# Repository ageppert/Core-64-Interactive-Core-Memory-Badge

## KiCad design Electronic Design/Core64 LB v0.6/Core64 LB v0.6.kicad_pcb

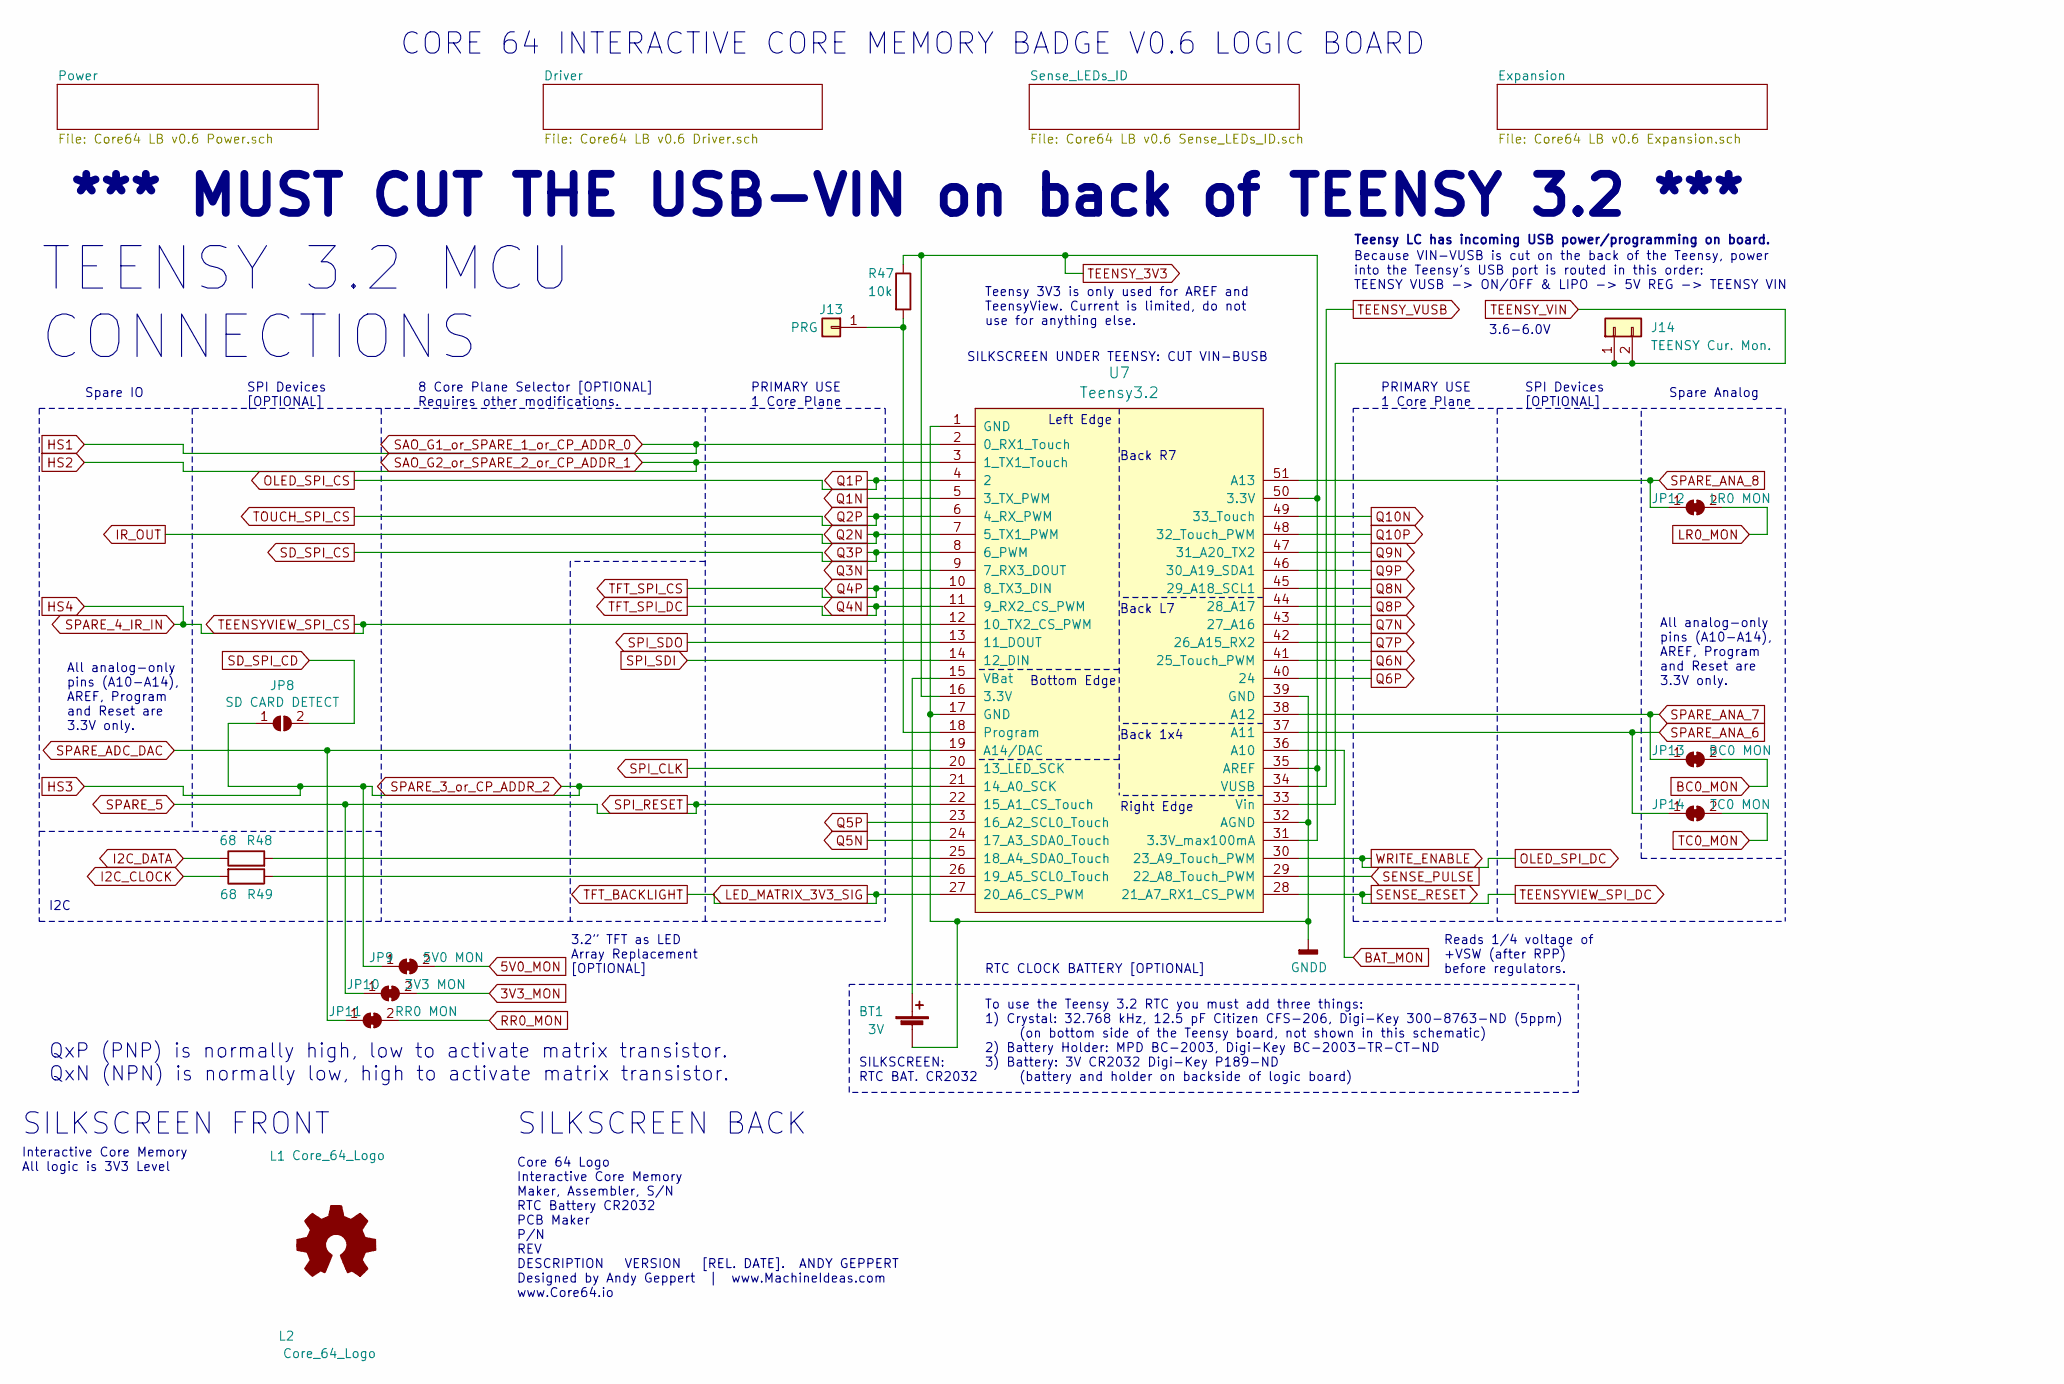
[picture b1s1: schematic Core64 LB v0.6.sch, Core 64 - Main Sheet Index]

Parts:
BT1: 3V; BatteryHolder_MPD_BC2003_1x2032; MPN MPD BC-2003
J13: PRG; PinSocket_1x01_P2.54mm_Vertical
J14: TEENSY Cur. Mon.; PinSocket_1x02_P2.54mm_Vertical
JP8: SD CARD DETECT; SolderJumper-2_P1.3mm_Open_RoundedPad1.0x1.5mm
JP9: 5V0 MON; SolderJumper-2_P1.3mm_Bridged_Pad1.0x1.5mm
JP10: 3V3 MON; SolderJumper-2_P1.3mm_Bridged_Pad1.0x1.5mm
JP11: RR0 MON; SolderJumper-2_P1.3mm_Bridged_Pad1.0x1.5mm
JP12: LR0 MON; SolderJumper-2_P1.3mm_Bridged_Pad1.0x1.5mm
JP13: BC0 MON; SolderJumper-2_P1.3mm_Bridged_Pad1.0x1.5mm
JP14: TC0 MON; SolderJumper-2_P1.3mm_Bridged_Pad1.0x1.5mm
L1: Core_64_Logo; Core64_Logo
L2: Core_64_Logo; Core64_Logo_9mm_tall
L4: Logo_Open_Hardware_Small; OSHW-Logo2_7.3x6mm_SilkScreen
R47: 10k; R_0805_2012Metric
R48, R49: 68; R_0805_2012Metric
U7: Teensy3.2; Teensy30_31_32_LC_SMD_SOCKETS

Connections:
3V3: JP10.2 (B); also elsewhere on the board
5V0: J14.1, J14.2, U7.33 (Vin); also elsewhere on the board
5V0_MON: JP9.2 (B); also elsewhere on the board
BAT_MON: U7.36 (A10); also elsewhere on the board
BC0_MON: JP13.2 (B); also elsewhere on the board
I2C_CLOCK: R49.2; also elsewhere on the board
I2C_DATA: R48.1; also elsewhere on the board
IR_OUT: U7.7 (5_TX1_PWM); also elsewhere on the board
LR0_MON: JP12.2 (B); also elsewhere on the board
unnamed: BT1.1 (+), U7.15 (VBat)
unnamed: J13.1, R47.2, U7.18 (Program)
unnamed: R48.2, U7.25 (18_A4_SDA0_Touch)
unnamed: R49.1, U7.26 (19_A5_SCL0_Touch)
OLED_SPI_CS: U7.4 (2); also elsewhere on the board
OLED_SPI_DC: U7.30 (23_A9_Touch_PWM); also elsewhere on the board
Q1N: U7.5 (3_TX_PWM); also elsewhere on the board
Q2P: U7.6 (4_RX_PWM); also elsewhere on the board
Q3N: U7.9 (7_RX3_DOUT); also elsewhere on the board
Q3P: U7.8 (6_PWM); also elsewhere on the board
Q4N: U7.11 (9_RX2_CS_PWM); also elsewhere on the board
Q4P: U7.10 (8_TX3_DIN); also elsewhere on the board
Q5N: U7.24 (17_A3_SDA0_Touch); also elsewhere on the board
Q5P: U7.23 (16_A2_SCL0_Touch); also elsewhere on the board
Q6N: U7.41 (25_Touch_PWM); also elsewhere on the board
Q6P: U7.40 (24); also elsewhere on the board
Q7N: U7.43 (27_A16); also elsewhere on the board
Q7P: U7.42 (26_A15_RX2); also elsewhere on the board
Q8N: U7.45 (29_A18_SCL1); also elsewhere on the board
Q8P: U7.44 (28_A17); also elsewhere on the board
Q9N: U7.47 (31_A20_TX2); also elsewhere on the board
Q9P: U7.46 (30_A19_SDA1); also elsewhere on the board
Q10N: U7.49 (33_Touch); also elsewhere on the board
Q10P: U7.48 (32_Touch_PWM); also elsewhere on the board
RR0_MON: JP11.2 (B); also elsewhere on the board
SD_SPI_CD: JP8.2 (B); also elsewhere on the board
SENSE_PULSE: U7.29 (22_A8_Touch_PWM); also elsewhere on the board
SENSE_RESET: U7.28 (21_A7_RX1_CS_PWM); also elsewhere on the board
SPARE_5: JP10.1 (A), U7.22 (15_A1_CS_Touch); also elsewhere on the board
SPARE_ADC_DAC: JP11.1 (A), U7.19 (A14/DAC); also elsewhere on the board
SPARE_ANA_6: JP14.1 (A), U7.37 (A11); also elsewhere on the board
SPARE_ANA_7: JP13.1 (A), U7.38 (A12); also elsewhere on the board
SPARE_ANA_8: JP12.1 (A), U7.51 (A13); also elsewhere on the board
SPI_CLK: U7.20 (13_LED_SCK); also elsewhere on the board
SPI_SDI: U7.14 (12_DIN); also elsewhere on the board
SPI_SDO: U7.13 (11_DOUT); also elsewhere on the board
TC0_MON: JP14.2 (B); also elsewhere on the board
TEENSY_3V3: R47.1, U7.16 (3.3V), U7.31 (3.3V_max100mA), U7.35 (AREF), U7.50 (3.3V); also elsewhere on the board
TEENSY_VUSB: U7.34 (VUSB); also elsewhere on the board

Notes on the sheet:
CORE 64 INTERACTIVE CORE MEMORY BADGE V0.6 LOGIC BOARD
Reads 1/4 voltage of +VSW (after RPP) before regulators.
Teensy LC has incoming USB power/programming on board.
TEENSY 3.2 MCU CONNECTIONS
*** MUST CUT THE USB-VIN on back of TEENSY 3.2 ***
Teensy 3V3 is only used for AREF and TeensyView. Current is limited, do not use for anything else.
PRIMARY USE 1 Core Plane
3.2” TFT as LED Array Replacement [OPTIONAL]
8 Core Plane Selector [OPTIONAL] Requires other modifications.
SILKSCREEN BACK
SILKSCREEN UNDER TEENSY: CUT VIN-BUSB
To use the Teensy 3.2 RTC you must add three things: 1) Crystal: 32.768 kHz, 12.5 pF Citizen CFS-206, Digi-Key 300-8763-ND (5ppm) (on bottom side of the Teensy board, not shown in this schematic) 2) Battery Holder: MPD BC-2003, Digi-Key BC-2003-TR-CT-ND 3) Battery: 3V CR2032 Digi-Key P189-ND (batte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
SILKSCREEN: RTC BAT. CR2032
SILKSCREEN FRONT
Core 64 Logo Interactive Core Memory Maker, Assembler, S/N RTC Battery CR2032 PCB Maker P/N REV DESCRIPTION VERSION [REL. DATE]. ANDY GEPPERT Designed by Andy Geppert | www.MachineIdeas.com www.Core64.io
Interactive Core Memory All logic is 3V3 Level
Spare Analog
Spare IO
SPI Devices [OPTIONAL]
RTC CLOCK BATTERY [OPTIONAL]
I2C
Because VIN-VUSB is cut on the back of the Teensy, power into the Teensy’s USB port is routed in this order: TEENSY VUSB -> ON/OFF & LIPO -> 5V REG -> TEENSY VIN
Left Edge
Bottom Edge
Right Edge
Back 1x4
Back L7
Back R7
QxP (PNP) is normally high, low to activate matrix transistor. QxN (NPN) is normally low, high to activate matrix transistor.
3.6-6.0V
All analog-only pins (A10-A14), AREF, Program and Reset are 3.3V only.

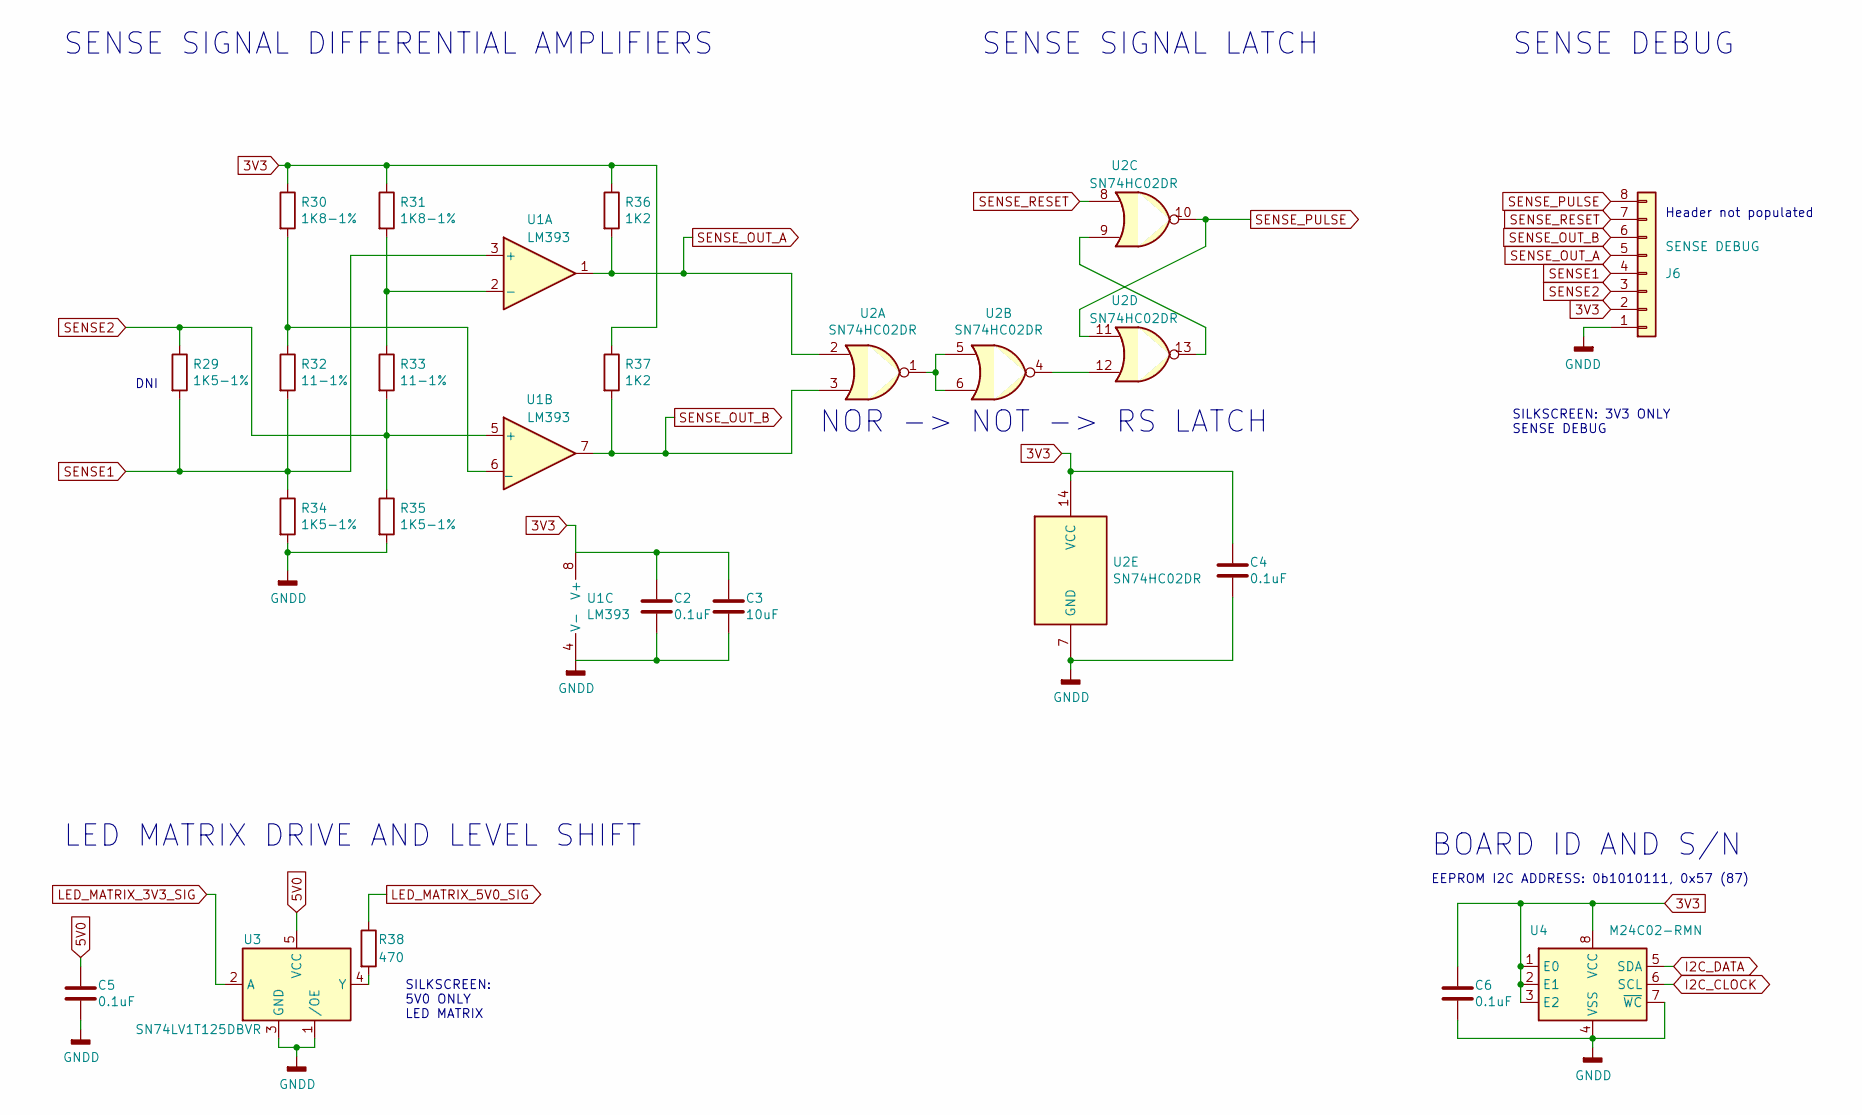
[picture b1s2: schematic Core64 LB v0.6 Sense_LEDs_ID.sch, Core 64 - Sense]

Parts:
C2, C4, C5, C6: 0.1uF; C_0805_2012Metric
C3: 10uF; C_0805_2012Metric
J6: SENSE DEBUG; PinSocket_1x08_P2.54mm_Vertical
R29, R34, R35: 1K5-1%; R_0805_2012Metric
R30, R31: 1K8-1%; R_0805_2012Metric
R32, R33: 11-1%; R_0805_2012Metric
R36, R37: 1K2; R_0805_2012Metric
R38: 470; R_0805_2012Metric
U1, U3: LM393; SOIC-8_W3.9mm; MPN LM393DT
U2: SN74HC02DR; SOIC-14_3.9x8.7mm_P1.27mm; MPN SN74HC02DR
U4: M24C02-RMN; SOIC-8_3.9x4.9mm_P1.27mm; MPN M24C02-WMN6TP

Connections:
3V3: C2.1, C3.1, C4.1, C6.1, J6.2, R30.1, R31.1, R36.1, R37.1, U1.8 (V+), U2.14 (VCC), U4.1 (E0), U4.2 (E1), U4.3 (E2), U4.8 (VCC); also elsewhere on the board
5V0: C5.1, U3.5 (VCC); also elsewhere on the board
I2C_CLOCK: U4.6 (SCL); also elsewhere on the board
I2C_DATA: U4.5 (SDA); also elsewhere on the board
LED_MATRIX_5V0_SIG: R38.1; also elsewhere on the board
unnamed: R30.2, R32.1, U1.6 (_)
unnamed: R38.2, U3.4 (Y)
unnamed: U2.1, U2.5, U2.6
unnamed: U2.4, U2.12
unnamed: U2.9, U2.13
SENSE2: J6.3, R29.1, R33.2, R35.1, U1.5 (+); also elsewhere on the board
SENSE_OUT_B: J6.6, R37.2, U1.7, U2.3
SENSE_PULSE: J6.8, U2.10, U2.11; also elsewhere on the board
SENSE_RESET: J6.7, U2.8; also elsewhere on the board

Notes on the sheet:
SENSE SIGNAL DIFFERENTIAL AMPLIFIERS
DNI
SENSE SIGNAL LATCH
SENSE DEBUG
SILKSCREEN: 3V3 ONLY SENSE DEBUG
NOR -> NOT -> RS LATCH
LED MATRIX DRIVE AND LEVEL SHIFT
SILKSCREEN: 5V0 ONLY LED MATRIX
BOARD ID AND S/N
EEPROM I2C ADDRESS: 0b1010111, 0x57 (87)
Header not populated

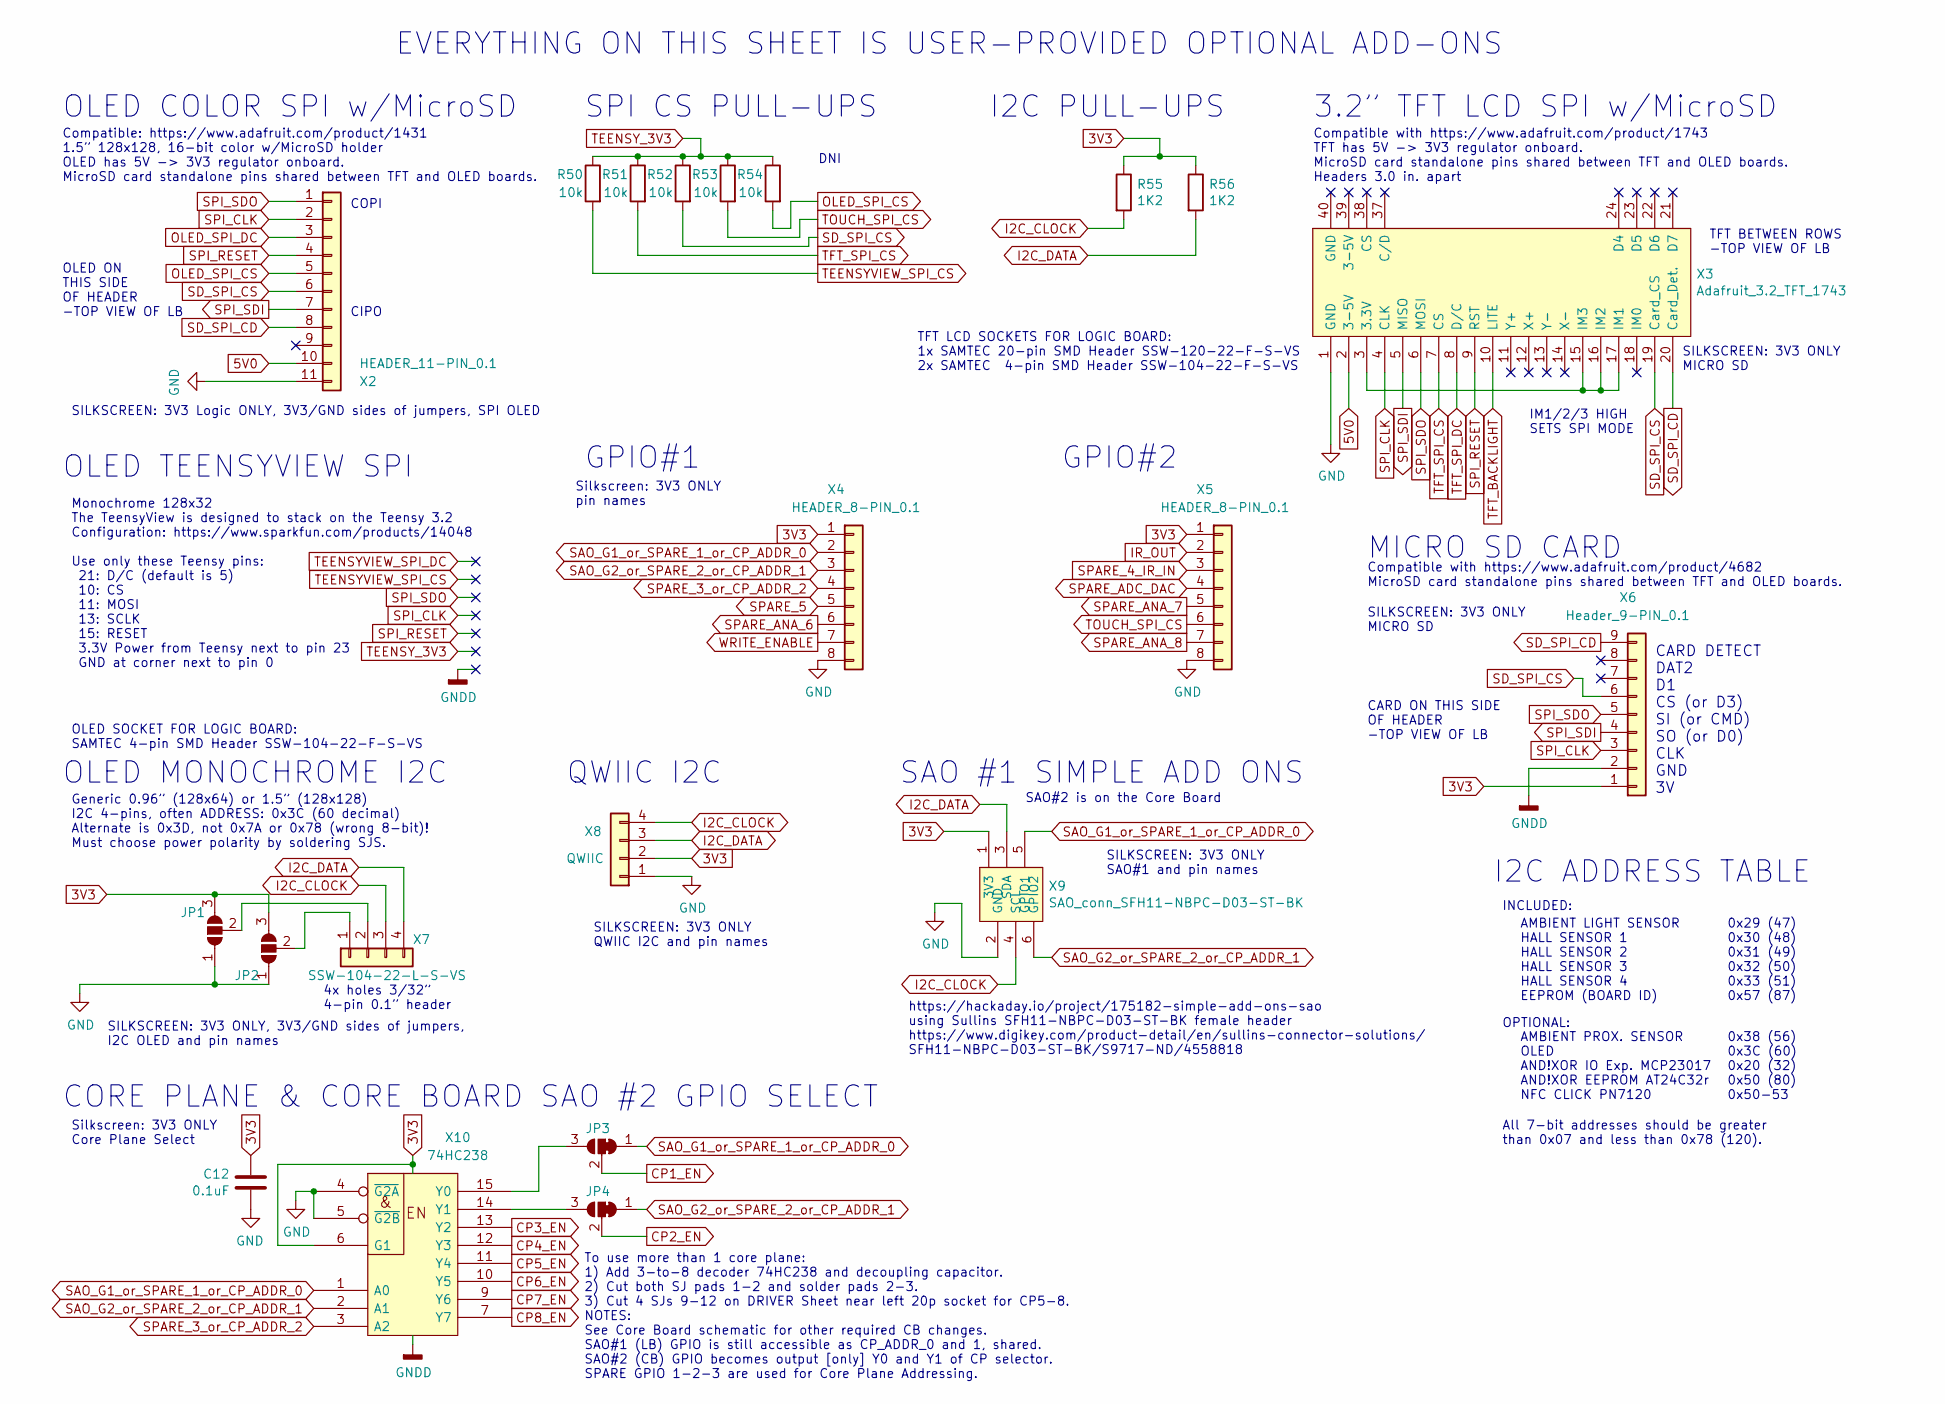
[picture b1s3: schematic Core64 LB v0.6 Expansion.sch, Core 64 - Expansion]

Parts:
C12: 0.1uF; C_0805_2012Metric
JP1, JP2: SolderJumper_3_Open; SolderJumper-3_P1.3mm_Open_Pad1.0x1.5mm_NumberLabels
JP3, JP4: SolderJumper_3_Open; SolderJumper-3_P1.3mm_Bridged12_RoundedPad1.0x1.5mm_NumberL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
R50, R51, R52, R53, R54: 10k; R_0805_2012Metric
R55, R56: 1K2; R_0805_2012Metric
X2: HEADER_11-PIN_0.1; PinSocket_1x11_P2.54mm_Vertical
X3: Adafruit_3.2_TFT_1743; Adafruit_3.2_TFT_Dual_PinHeader_1x20_P2.54mm_Vertical_SMD_P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; Manufacturer_Part_Number MIKROE-971; Mouser Part Number 932-MIKROE-971
X4, X5: HEADER_8-PIN_0.1; PinSocket_1x08_P2.54mm_Vertical
X6: Header_9-PIN_0.1; PinSocket_1x09_P2.54mm_Vertical
X7: SSW-104-22-L-S-VS; PinSocket_1x04_P2.54mm_Vertical_SMD_and_TH_Pin1Left
X8: QWIIC; JST_SH_SM04B-SRSS-TB_1x04-1MP_P1.00mm_Horizontal; MPN SM04B-SRSS-TB(LF)(SN)
X9: SAO_conn_SFH11-NBPC-D03-ST-BK; Badgelife-SAOv169-BADGE-2x3; MPN SFH11-NBPC-D03-ST-BK
X10: 74HC238; TSSOP-16-W4.40mm

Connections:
3V3: C12.1, JP1.3 (B), JP2.3 (B), R55.1, R56.1, X4.1, X5.1, X6.1, X8.2, X9.1 (3V3), X10.6 (G1), X10.16 (VCC); also elsewhere on the board
5V0: X2.10, X3.2 (3-5V); also elsewhere on the board
I2C_CLOCK: R55.2, X7.3, X8.4, X9.4 (SCL); also elsewhere on the board
I2C_DATA: R56.2, X7.4, X8.3, X9.3 (SDA); also elsewhere on the board
IR_OUT: X5.2; also elsewhere on the board
unnamed: X3.3 (3.3V), X3.15 (IM3), X3.16 (IM2), X3.17 (IM1)
unnamed: JP4.3 (B), X10.14 (Y1)
unnamed: JP3.3 (B), X10.15 (Y0)
OLED_SPI_CS: R54.2, X2.5; also elsewhere on the board
OLED_SPI_DC: X2.3, X4.7; also elsewhere on the board
Q2P: R53.2, X5.6; also elsewhere on the board
Q3P: R52.2, X2.6, X3.19 (Card_CS), X6.6; also elsewhere on the board
Q4N: X3.8 (D/C); also elsewhere on the board
Q4P: R51.2, X3.7 (CS); also elsewhere on the board
SD_SPI_CD: X2.8, X3.20 (Card_Det.), X6.9; also elsewhere on the board
SPARE_5: X2.4, X3.9 (RST), X4.5; also elsewhere on the board
SPARE_ADC_DAC: X5.4; also elsewhere on the board
SPARE_ANA_6: X4.6; also elsewhere on the board
SPARE_ANA_7: X5.5; also elsewhere on the board
SPARE_ANA_8: X5.7; also elsewhere on the board
SPI_CLK: X2.2, X3.4 (CLK), X6.3; also elsewhere on the board
SPI_SDI: X2.7, X3.5 (MISO), X6.4; also elsewhere on the board
SPI_SDO: X2.1, X3.6 (MOSI), X6.5; also elsewhere on the board
TEENSY_3V3: R50.1, R51.1, R52.1, R53.1, R54.1; also elsewhere on the board

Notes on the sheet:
CORE PLANE & CORE BOARD SAO #2 GPIO SELECT
SAO #1 SIMPLE ADD ONS
OLED MONOCHROME I2C
Generic 0.96” (128x64) or 1.5” (128x128) I2C 4-pins, often ADDRESS: 0x3C (60 decimal) Alternate is 0x3D, not 0x7A or 0x78 (wrong 8-bit)! Must choose power polarity by soldering SJS.
https://hackaday.io/project/175182-simple-add-ons-sao using Sullins SFH11-NBPC-D03-ST-BK female header https://www.digikey.com/product-detail/en/sullins-connector-solutions/ SFH11-NBPC-D03-ST-BK/S9717-ND/4558818
QWIIC I2C
MICRO SD CARD
Compatible with https://www.adafruit.com/product/4682 MicroSD card standalone pins shared between TFT and OLED boards.
SILKSCREEN: 3V3 ONLY, 3V3/GND sides of jumpers, I2C OLED and pin names
SILKSCREEN: 3V3 ONLY SAO#1 and pin names
Silkscreen: 3V3 ONLY pin names
OLED COLOR SPI w/MicroSD
3.2” TFT LCD SPI w/MicroSD
GPIO#1
EVERYTHING ON THIS SHEET IS USER-PROVIDED OPTIONAL ADD-ONS
To use more than 1 core plane: 1) Add 3-to-8 decoder 74HC238 and decoupling capacitor. 2) Cut both SJ pads 1-2 and solder pads 2-3. 3) Cut 4 SJs 9-12 on DRIVER Sheet near left 20p socket for CP5-8. NOTES: See Core Board schematic for other required CB changes. SAO#1 (LB) GPIO is still accessible as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
Silkscreen: 3V3 ONLY Core Plane Select
4x holes 3/32” 4-pin 0.1” header
SILKSCREEN: 3V3 ONLY QWIIC I2C and pin names
SILKSCREEN: 3V3 Logic ONLY, 3V3/GND sides of jumpers, SPI OLED
SILKSCREEN: 3V3 ONLY MICRO SD
SAO#2 is on the Core Board
CARD ON THIS SIDE OF HEADER -TOP VIEW OF LB
GPIO#2
Compatible with https://www.adafruit.com/product/1743 TFT has 5V -> 3V3 regulator onboard. MicroSD card standalone pins shared between TFT and OLED boards. Headers 3.0 in. apart
All 7-bit addresses should be greater than 0x07 and less than 0x78 (120).
AMBIENT LIGHT SENSOR HALL SENSOR 1 HALL SENSOR 2 HALL SENSOR 3 HALL SENSOR 4 EEPROM (BOARD ID)
0x29 (47) 0x30 (48) 0x31 (49) 0x32 (50) 0x33 (51) 0x57 (87)
INCLUDED:
OPTIONAL:
AMBIENT PROX. SENSOR OLED AND!XOR IO Exp. MCP23017 AND!XOR EEPROM AT24C32r NFC CLICK PN7120
0x38 (56) 0x3C (60) 0x20 (32) 0x50 (80) 0x50-53
I2C ADDRESS TABLE
OLED TEENSYVIEW SPI
Monochrome 128x32 The TeensyView is designed to stack on the Teensy 3.2 Configuration: https://www.sparkfun.com/products/14048 Use only these Teensy pins: 21: D/C (default is 5) 10: CS 11: MOSI 13: SCLK 15: RESET 3.3V Power from Teensy next to pin 23 GND at corner next to pin 0
Compatible: https://www.adafruit.com/product/1431 1.5” 128x128, 16-bit color w/MicroSD holder OLED has 5V -> 3V3 regulator onboard. MicroSD card standalone pins shared between TFT and OLED boards.
OLED ON THIS SIDE OF HEADER -TOP VIEW OF LB
I2C PULL-UPS
SPI CS PULL-UPS
DNI

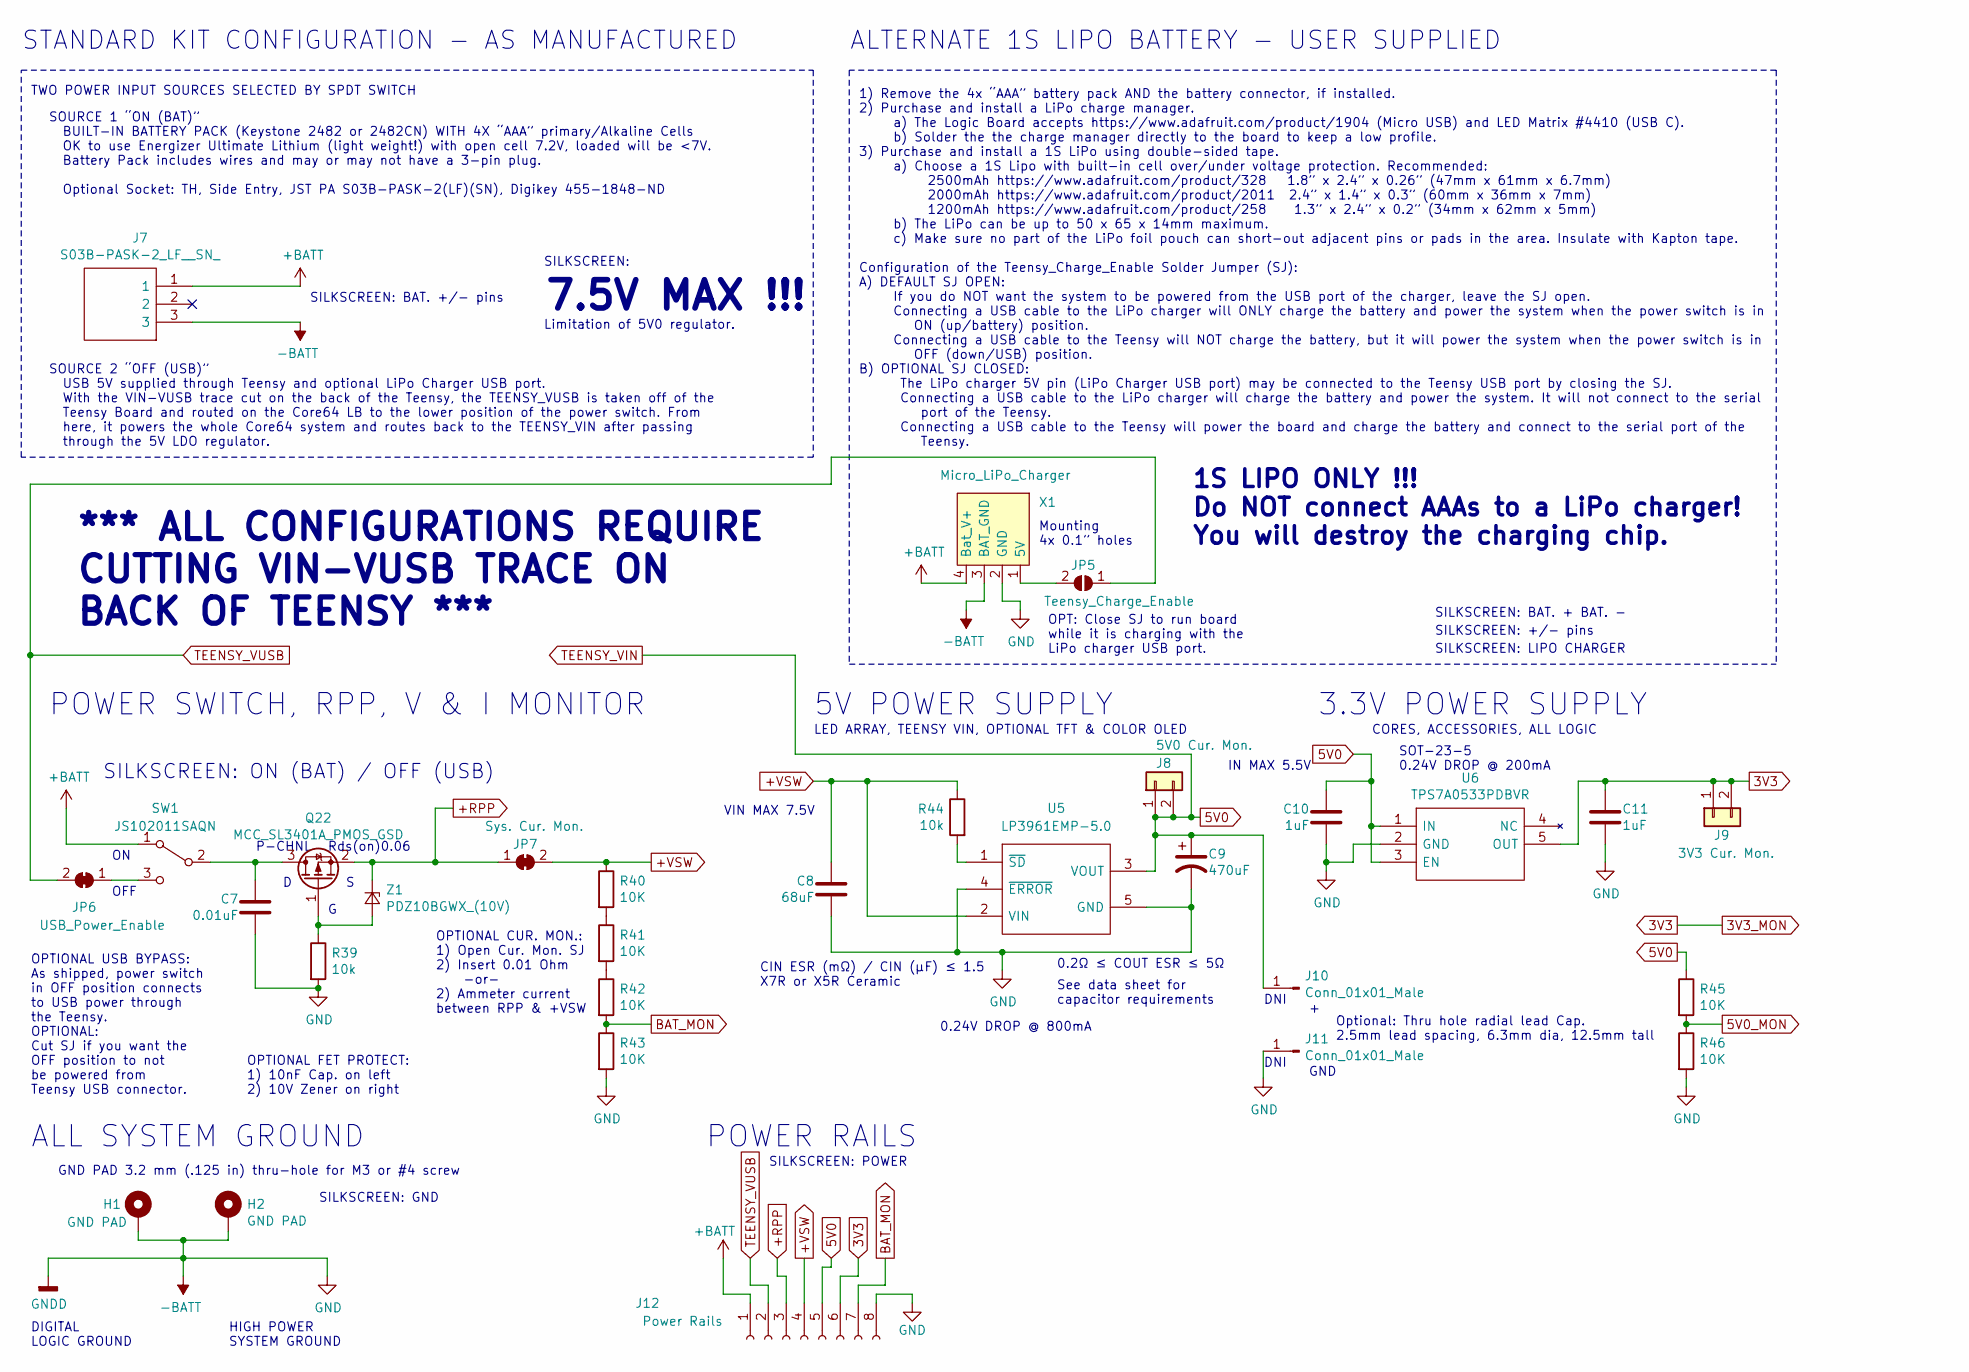
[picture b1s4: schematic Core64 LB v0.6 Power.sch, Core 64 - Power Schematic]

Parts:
C7: 0.01uF; C_0805_2012Metric
C8: 68uF; C_1206_3216Metric; MPN C3216X5R1A686M160AC
C9: 470uF; CP_Elec_6.3x7.7; MPN(Secondary) 6.3SEV330M6.3X8; Digikey 565-EMHL100ARA471MHA0GCT-ND
C10, C11: 1uF; C_0805_2012Metric
H1, H2: GND PAD; MountingHole_3.2mm_M3_Pad_Via
J7: S03B-PASK-2_LF__SN_; S03BPASK2LFSN_.075in_holes; Manufacturer_Part_Number S03B-PASK-2(LF)(SN)
J8: 5V0 Cur. Mon.; PinSocket_1x02_P2.54mm_Vertical
J9: 3V3 Cur. Mon.; PinSocket_1x02_P2.54mm_Vertical; MPN SN74HC02DR
J10, J11: Conn_01x01_Male; PinHeader_1x01_P2.54mm_Vertical_No_Registration
J12: Power Rails; PinSocket_1x08_P2.54mm_Vertical
JP5: Teensy_Charge_Enable; SolderJumper-2_P1.3mm_Open_RoundedPad1.0x1.5mm
JP6: USB_Power_Enable; SolderJumper-2_P1.3mm_Bridged_RoundedPad1.0x1.5mm
JP7: Sys. Cur. Mon.; SolderJumper-2_P1.3mm_Bridged_Pad1.0x1.5mm
Q22: MCC_SL3401A_PMOS_GSD; SOT-23-3; MPN SL3401A-TP
R39, R44: 10k; R_0805_2012Metric
R40, R41, R42, R43, R45, R46: 10K; R_0805_2012Metric
SW1: JS102011SAQN; SW_SPDT_CK-JS102011SAQN_Core64_Recessed; MPN JS102011SAQN
U5: LP3961EMP-5.0; SOT150P696X180-5N; Manufacturer_Part_Number LP3961EMP-5.0; Mouser Part Number 926-LP3961EMP-50
U6: TPS7A0533PDBVR; SOT95P280X145-5N; Manufacturer_Part_Number TPS7A0533PDBVR; Mouser Part Number 595-TPS7A0533PDBVR
X1: Micro_LiPo_Charger; Micro_LiPo_Charger_CornerSMD
Z1: PDZ10BGWX_(10V); SOD-123

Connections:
3V3: C11.1, J9.1, J9.2, J12.6, U6.5 (OUT); also elsewhere on the board
5V0: C9.1, C10.1, J8.1, J8.2, J10.1, J12.5, R45.1, U5.3 (VOUT), U6.1 (IN), U6.3 (EN); also elsewhere on the board
5V0_MON: R45.2, R46.1; also elsewhere on the board
+BATT: J7.1, J12.1, SW1.1 (A), X1.4 (Bat_V+); also elsewhere on the board
+RPP: J12.3, JP7.1 (A), Q22.2 (S), Z1.1 (K)
+VSW: C8.1, J12.4, JP7.2 (B), R40.1, R44.1, U5.2 (VIN)
BAT_MON: J12.7, R42.2, R43.1; also elsewhere on the board
unnamed: C7.1, Q22.3 (D), SW1.2 (B)
unnamed: JP5.2 (B), X1.1 (5V)
unnamed: JP6.1 (A), SW1.3 (C)
unnamed: Q22.1 (G), R39.1, Z1.2 (A)
unnamed: R40.2, R41.1
unnamed: R41.2, R42.1
unnamed: R44.2, U5.1 (~SD)
TEENSY_VUSB: J12.2, JP5.1 (A), JP6.2 (B); also elsewhere on the board

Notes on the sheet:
CORES, ACCESSORIES, ALL LOGIC
SOURCE 1 “ON (BAT)” BUILT-IN BATTERY PACK (Keystone 2482 or 2482CN) WITH 4X “AAA” primary/Alkaline Cells OK to use Energizer Ultimate Lithium (light weight!) with open cell 7.2V, loaded will be <7V. Battery Pack includes wires and may or may not have a 3-pin plug. Optional Socket: TH, Side Entry, J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
SOURCE 2 “OFF (USB)” USB 5V supplied through Teensy and optional LiPo Charger USB port. With the VIN-VUSB trace cut on the back of the Teensy, the TEENSY_VUSB is taken off of the Teensy Board and routed on the Core64 LB to the lower position of the power switch. From here, it powers the whole Core6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
TWO POWER INPUT SOURCES SELECTED BY SPDT SWITCH
STANDARD KIT CONFIGURATION - AS MANUFACTURED
ALTERNATE 1S LIPO BATTERY - USER SUPPLIED
POWER SWITCH, RPP, V & I MONITOR
3.3V POWER SUPPLY
LED ARRAY, TEENSY VIN, OPTIONAL TFT & COLOR OLED
ALL SYSTEM GROUND
POWER RAILS
HIGH POWER SYSTEM GROUND
DIGITAL LOGIC GROUND
OPTIONAL USB BYPASS: As shipped, power switch in OFF position connects to USB power through the Teensy. OPTIONAL: Cut SJ if you want the OFF position to not be powered from Teensy USB connector.
SILKSCREEN: ON (BAT) / OFF (USB)
7.5V MAX !!!
SILKSCREEN: BAT. +/- pins
OPTIONAL CUR. MON.: 1) Open Cur. Mon. SJ 2) Insert 0.01 Ohm -or- 2) Ammeter current between RPP & +VSW
5V POWER SUPPLY
P-CHNL
*** ALL CONFIGURATIONS REQUIRE CUTTING VIN-VUSB TRACE ON BACK OF TEENSY ***
1S LIPO ONLY !!! Do NOT connect AAAs to a LiPo charger! You will destroy the charging chip.
OPTIONAL FET PROTECT: 1) 10nF Cap. on left 2) 10V Zener on right
SILKSCREEN: +/- pins
1) Remove the 4x “AAA” battery pack AND the battery connector, if installed. 2) Purchase and install a LiPo charge manager. a) The Logic Board accepts https://www.adafruit.com/product/1904 (Micro USB) and LED Matrix #4410 (USB C). b) Solder the the charge manager directly to the board to keep a low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
OPT: Close SJ to run board while it is charging with the LiPo charger USB port.
SOT-23-5 0.24V DROP @ 200mA
CIN ESR (mΩ) / CIN (μF) ≤ 1.5 X7R or X5R Ceramic
0.2Ω ≤ COUT ESR ≤ 5Ω
See data sheet for capacitor requirements
GND PAD 3.2 mm (.125 in) thru-hole for M3 or #4 screw
SILKSCREEN: GND
SILKSCREEN: LIPO CHARGER
SILKSCREEN: BAT. + BAT. -
SILKSCREEN: POWER
Mounting 4x 0.1” holes
SILKSCREEN:
Limitation of 5V0 regulator.
OFF
Rds(on)0.06
